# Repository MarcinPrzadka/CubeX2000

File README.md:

CubeX 2000 jest  to super nowoczesny led cube 8x8x8 sterowany za pomocą Atmega32.
Celem projektu jest utworzenie okiengowego programu komputerowego który będzię łaczył się z uC poprzez UART oraz umożliwiał użytkownikowi tworzenie nowych animacji oraz ich zapis i odczyt z pliku.

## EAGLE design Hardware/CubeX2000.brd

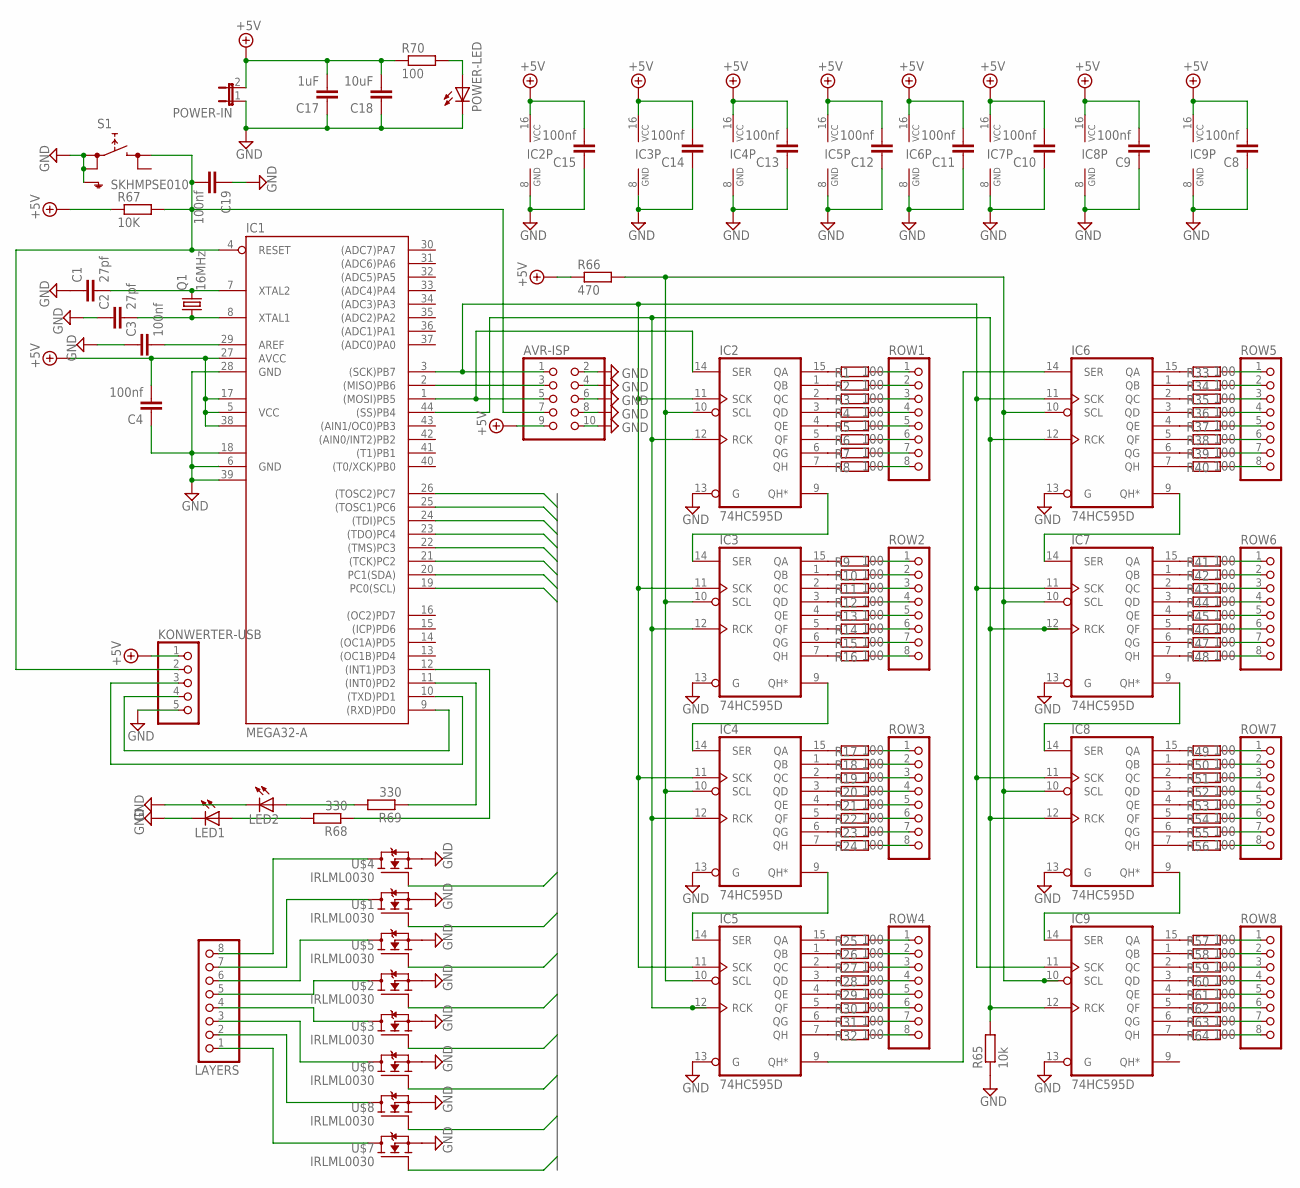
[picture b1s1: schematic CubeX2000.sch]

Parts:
AVR-ISP: PINHD-2X5; 2X05
C1, C2: 27pf; C1206
C3, C4, C8, C9, C10, C11, C12, C13, C14, C15, C19: 100nf; C1206
C17: 1uF; C1206
C18: 10uF; C1206
IC1: MEGA32-A; TQFP44
IC2, IC3, IC4, IC5, IC6, IC7, IC8, IC9: 74HC595D; SO16
KONWERTER-USB: PINHD-1X5; 1X05
LAYERS: PINHD-1X8; 1X08
LED1, LED2: LEDSMT1206; 1206
POWER-IN: JP1E; JP1
POWER-LED: LEDSMT1206; 1206
Q1: 16MHz; HC49/S
R1, R2, R3, R4, R5, R6, R7, R8, R9, R10, R11, R12, R13, R14, R15, R16, R17, R18, R19, R20, R21, R22, R23, R24, R25, R26, R27, R28, R29, R30, R31, R32, R33, R34, R35, R36, R37, R38, R39, R40, R41, R42, R43, R44, R45, R46, R47, R48, R49, R50, R51, R52, R53, R54, R55, R56, R57, R58, R59, R60, R61, R62, R63, R64, R70: 100; R1206
R65: 10k; R1206
R66: 470; R1206
R67: 10K; R1206
R68, R69: 330; R1206
ROW1, ROW2, ROW3, ROW4, ROW5, ROW6, ROW7, ROW8: PINHD-1X8; 1X08
S1: SKHMPSE010; SKHMPXE010
U$1, U$2, U$3, U$4, U$5, U$6, U$7, U$8: IRLML0030; SOT23

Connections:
+5V: AVR-ISP.9, C4.2, C8.2, C9.2, C10.2, C11.2, C12.2, C13.2, C14.2, C15.2, C17.2, C18.2, IC1.5 (VCC), IC1.17 (VCC1), IC1.27 (AVCC), IC1.38 (VCC2), IC2.16 (VCC), IC3.16 (VCC), IC4.16 (VCC), IC5.16 (VCC), IC6.16 (VCC), IC7.16 (VCC), IC8.16 (VCC), IC9.16 (VCC), KONWERTER-USB.1, POWER-IN.2, R66.1, R67.1, R70.1
GND: AVR-ISP.2, AVR-ISP.4, AVR-ISP.6, AVR-ISP.8, AVR-ISP.10, C1.1, C2.1, C3.1, C4.1, C8.1, C9.1, C10.1, C11.1, C12.1, C13.1, C14.1, C15.1, C17.1, C18.1, C19.1, IC1.6 (GND), IC1.18 (GND1), IC1.28 (GND), IC1.39 (GND2), IC2.8 (GND), IC2.13 (G), IC3.8 (GND), IC3.13 (G), IC4.8 (GND), IC4.13 (G), IC5.8 (GND), IC5.13 (G), IC6.8 (GND), IC6.13 (G), IC7.8 (GND), IC7.13 (G), IC8.8 (GND), IC8.13 (G), IC9.8 (GND), IC9.13 (G), KONWERTER-USB.5, LED1.C, LED2.C, POWER-IN.1, POWER-LED.C, R65.1, S1.1 (1.1), S1.2 (1.2), S1.5 (SH), U$1.2 (S), U$2.2 (S), U$3.2 (S), U$4.2 (S), U$5.2 (S), U$6.2 (S), U$7.2 (S), U$8.2 (S)
LAYERS1: IC1.19 (PC0(SCL)), U$7.1 (G)
LAYERS2: IC1.20 (PC1(SDA)), U$8.1 (G)
LAYERS3: IC1.21 ((TCK)PC2), U$6.1 (G)
LAYERS4: IC1.22 ((TMS)PC3), U$3.1 (G)
LAYERS5: IC1.23 ((TDO)PC4), U$2.1 (G)
LAYERS6: IC1.24 ((TDI)PC5), U$5.1 (G)
LAYERS7: IC1.25 ((TOSC1)PC6), U$1.1 (G)
LAYERS8: IC1.26 ((TOSC2)PC7), U$4.1 (G)
unnamed: IC2.15 (QA), R1.1
unnamed: IC2.1 (QB), R2.1
unnamed: IC2.2 (QC), R3.1
unnamed: IC2.3 (QD), R4.1
unnamed: IC2.4 (QE), R5.1
unnamed: IC2.5 (QF), R6.1
unnamed: IC2.6 (QG), R7.1
unnamed: IC2.7 (QH), R8.1
unnamed: IC3.15 (QA), R9.1
unnamed: IC3.1 (QB), R10.1
unnamed: IC3.2 (QC), R11.1
unnamed: IC3.3 (QD), R12.1
unnamed: IC3.4 (QE), R13.1
unnamed: IC3.5 (QF), R14.1
unnamed: IC3.6 (QG), R15.1
unnamed: IC3.7 (QH), R16.1
unnamed: IC4.15 (QA), R17.1
unnamed: IC4.1 (QB), R18.1
unnamed: IC4.2 (QC), R19.1
unnamed: IC4.3 (QD), R20.1
unnamed: IC4.4 (QE), R21.1
unnamed: IC4.5 (QF), R22.1
unnamed: IC4.6 (QG), R23.1
unnamed: IC4.7 (QH), R24.1
unnamed: IC5.15 (QA), R25.1
unnamed: IC5.1 (QB), R26.1
unnamed: IC5.2 (QC), R27.1
unnamed: IC5.3 (QD), R28.1
unnamed: IC5.4 (QE), R29.1
unnamed: IC5.5 (QF), R30.1
unnamed: IC5.6 (QG), R31.1
unnamed: IC5.7 (QH), R32.1
unnamed: IC6.15 (QA), R33.1
unnamed: IC6.1 (QB), R34.1
unnamed: IC6.2 (QC), R35.1
unnamed: IC6.3 (QD), R36.1
unnamed: IC6.4 (QE), R37.1
unnamed: IC6.5 (QF), R38.1
unnamed: IC6.6 (QG), R39.1
unnamed: IC6.7 (QH), R40.1
unnamed: IC7.15 (QA), R41.1
unnamed: IC7.1 (QB), R42.1
unnamed: IC7.2 (QC), R43.1
unnamed: IC7.3 (QD), R44.1
unnamed: IC7.4 (QE), R45.1
unnamed: IC7.5 (QF), R46.1
unnamed: IC7.6 (QG), R47.1
unnamed: IC7.7 (QH), R48.1
unnamed: IC8.15 (QA), R49.1
unnamed: IC8.1 (QB), R50.1
unnamed: IC8.2 (QC), R51.1
unnamed: IC8.3 (QD), R52.1
unnamed: IC8.4 (QE), R53.1
unnamed: IC8.5 (QF), R54.1
unnamed: IC8.6 (QG), R55.1
unnamed: IC8.7 (QH), R56.1
unnamed: IC9.15 (QA), R57.1
unnamed: IC9.1 (QB), R58.1
unnamed: IC9.2 (QC), R59.1
unnamed: IC9.3 (QD), R60.1
unnamed: IC9.4 (QE), R61.1
unnamed: IC9.5 (QF), R62.1
unnamed: IC9.6 (QG), R63.1
unnamed: IC9.7 (QH), R64.1
unnamed: R1.2, ROW1.1
unnamed: R2.2, ROW1.2
unnamed: R3.2, ROW1.3
unnamed: R4.2, ROW1.4
unnamed: R5.2, ROW1.5
unnamed: R6.2, ROW1.6
unnamed: R7.2, ROW1.7
unnamed: R8.2, ROW1.8
unnamed: R9.2, ROW2.1
unnamed: R10.2, ROW2.2
unnamed: R11.2, ROW2.3
unnamed: R12.2, ROW2.4
unnamed: R13.2, ROW2.5
unnamed: R14.2, ROW2.6
unnamed: R15.2, ROW2.7
unnamed: R16.2, ROW2.8
unnamed: R17.2, ROW3.1
unnamed: R18.2, ROW3.2
unnamed: R19.2, ROW3.3
unnamed: R20.2, ROW3.4
unnamed: R21.2, ROW3.5
unnamed: R22.2, ROW3.6
unnamed: R23.2, ROW3.7
unnamed: R24.2, ROW3.8
unnamed: R25.2, ROW4.1
unnamed: R26.2, ROW4.2
unnamed: R27.2, ROW4.3
unnamed: R28.2, ROW4.4
unnamed: R29.2, ROW4.5
unnamed: R30.2, ROW4.6
unnamed: R31.2, ROW4.7
unnamed: R32.2, ROW4.8
unnamed: R33.2, ROW5.1
unnamed: R34.2, ROW5.2
unnamed: R35.2, ROW5.3
unnamed: R36.2, ROW5.4
unnamed: R37.2, ROW5.5
unnamed: R38.2, ROW5.6
unnamed: R39.2, ROW5.7
unnamed: R40.2, ROW5.8
unnamed: R41.2, ROW6.1
unnamed: R42.2, ROW6.2
unnamed: R43.2, ROW6.3
unnamed: R44.2, ROW6.4
unnamed: R45.2, ROW6.5
unnamed: R46.2, ROW6.6
unnamed: R47.2, ROW6.7
unnamed: R48.2, ROW6.8
unnamed: R49.2, ROW7.1
unnamed: R50.2, ROW7.2
unnamed: R51.2, ROW7.3
unnamed: R52.2, ROW7.4
unnamed: R53.2, ROW7.5
unnamed: R54.2, ROW7.6
unnamed: R55.2, ROW7.7
unnamed: R56.2, ROW7.8
unnamed: R57.2, ROW8.1
unnamed: R58.2, ROW8.2
unnamed: R59.2, ROW8.3
unnamed: R60.2, ROW8.4
unnamed: R61.2, ROW8.5
unnamed: R62.2, ROW8.6
unnamed: R63.2, ROW8.7
unnamed: R64.2, ROW8.8
unnamed: IC8.9 (QH*), IC9.14 (SER)
unnamed: IC7.9 (QH*), IC8.14 (SER)
unnamed: IC6.9 (QH*), IC7.14 (SER)
unnamed: IC4.9 (QH*), IC5.14 (SER)
unnamed: IC3.9 (QH*), IC4.14 (SER)
unnamed: IC2.9 (QH*), IC3.14 (SER)
unnamed: IC5.9 (QH*), IC6.14 (SER)
unnamed: AVR-ISP.1, IC1.3 ((SCK)PB7), IC2.11 (SCK), IC3.11 (SCK), IC4.11 (SCK), IC5.11 (SCK), IC6.11 (SCK), IC7.11 (SCK), IC8.11 (SCK), IC9.11 (SCK)
unnamed: AVR-ISP.5, IC1.1 ((MOSI)PB5), IC2.14 (SER)
unnamed: IC2.10 (SCL), IC3.10 (SCL), IC4.10 (SCL), IC5.10 (SCL), IC6.10 (SCL), IC7.10 (SCL), IC8.10 (SCL), IC9.10 (SCL), R66.2
unnamed: LAYERS.5, U$2.3 (D)
unnamed: IC1.44 ((SS)PB4), IC2.12 (RCK), IC3.12 (RCK), IC4.12 (RCK), IC5.12 (RCK), IC6.12 (RCK), IC7.12 (RCK), IC8.12 (RCK), IC9.12 (RCK), R65.2
unnamed: AVR-ISP.3, IC1.2 ((MISO)PB6)
unnamed: IC1.9 ((RXD)PD0), KONWERTER-USB.4
unnamed: IC1.10 ((TXD)PD1), KONWERTER-USB.3
unnamed: C1.2, IC1.7 (XTAL2), Q1.2
unnamed: C2.2, IC1.8 (XTAL1), Q1.1
unnamed: C3.2, IC1.29 (AREF)
unnamed: LED1.A, R68.2
unnamed: LED2.A, R69.2
unnamed: IC1.11 ((INT0)PD2), R69.1
unnamed: IC1.12 ((INT1)PD3), R68.1
unnamed: LAYERS.6, U$5.3 (D)
unnamed: AVR-ISP.7, C19.2, IC1.4 (RESET), KONWERTER-USB.2, R67.2, S1.3 (2.1)
unnamed: LAYERS.7, U$1.3 (D)
unnamed: LAYERS.8, U$4.3 (D)
unnamed: LAYERS.4, U$3.3 (D)
unnamed: LAYERS.3, U$6.3 (D)
unnamed: LAYERS.2, U$8.3 (D)
unnamed: LAYERS.1, U$7.3 (D)
unnamed: POWER-LED.A, R70.2

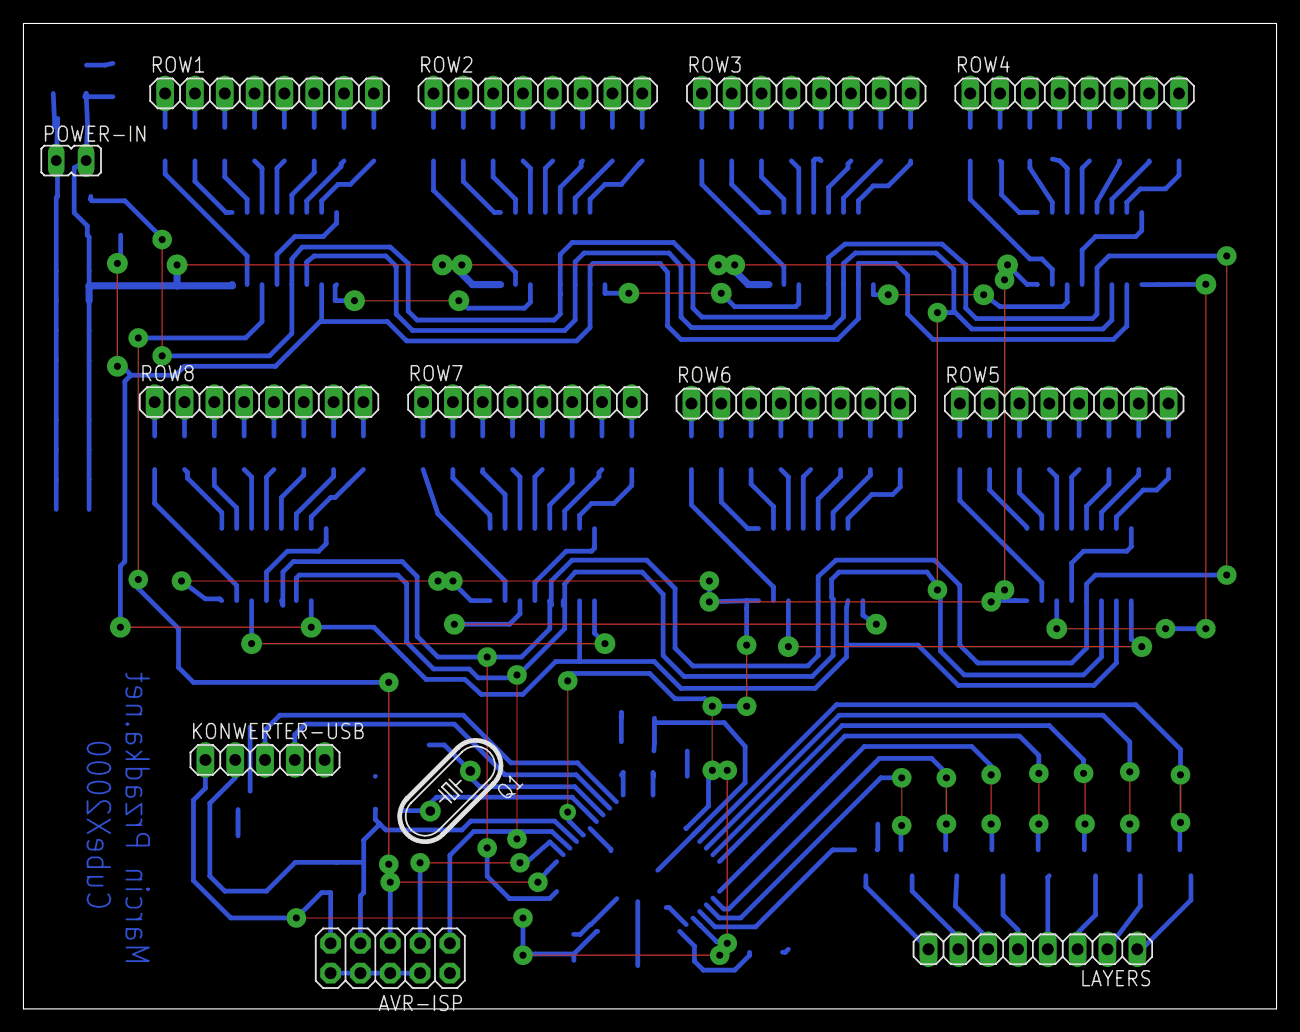
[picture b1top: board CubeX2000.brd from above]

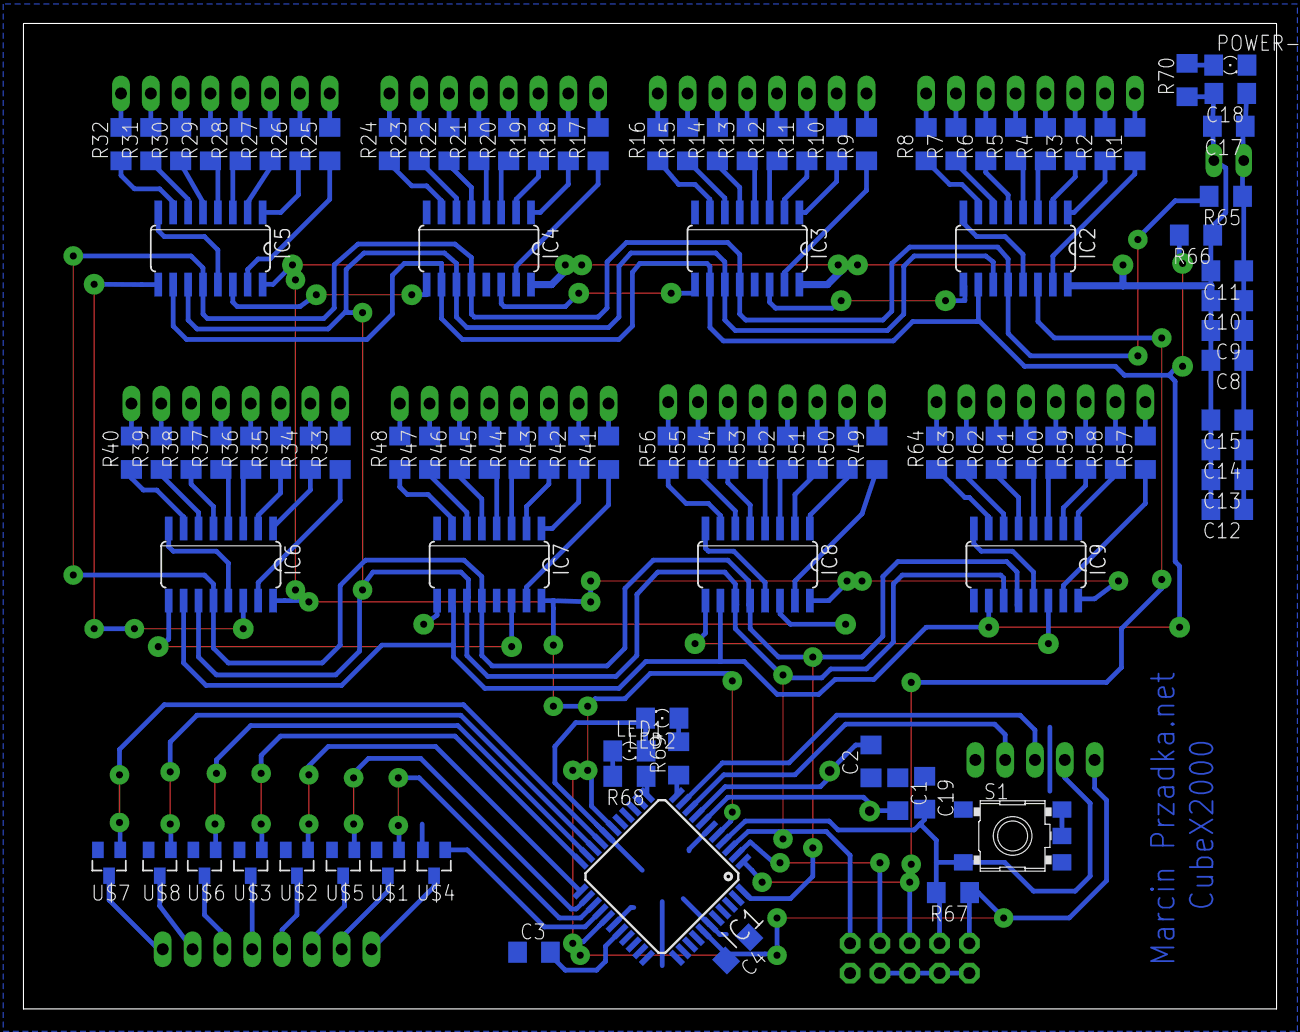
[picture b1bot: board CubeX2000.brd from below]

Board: 2 copper layers, 106.7 x 83.9 mm, 119 parts (106 on the bottom side), 169 nets.
